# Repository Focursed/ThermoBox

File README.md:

# ThermoBox — карманный термометр с играми на одну кнопку

**Автор:** Igor Novohatskiy, 2026

Маленькая коробочка: экран 0,96" OLED, датчик SHT40, аккумулятор LiPo, зарядка от USB‑C,
боковая кнопка будит устройство из глубокого сна. Программируется через тот же USB‑C прямо из Arduino IDE.

## Схема электрическая принципиальная

Схема в PDF: [docs/ThermoBox_schematic.pdf](docs/ThermoBox_schematic.pdf) · исходник KiCad 10: [ThermoBox.kicad_sch](ThermoBox.kicad_sch)

## Печатная плата

## Структура проекта

| Путь | Что внутри |
|---|---|
| `ThermoBox.kicad_pro / .kicad_sch / .kicad_pcb` | проект KiCad 10 (схема + плата) |
| `docs/schematic.png`, `docs/ThermoBox_schematic.pdf` | схема (картинка и PDF) |
| `docs/ThermoBox_pcb_top.pdf`, `docs/board_*_3d.png` | плата |
| `fab/gerbers/` | Gerber + сверловка для заказа (JLCPCB/PCBWay: заархивируй папку в zip) |
| `fab/ThermoBox_BOM.csv`, `fab/ThermoBox_positions.csv` | список компонентов и координаты для сборки |
| `fusion/` | **STEP, DXF контура и все размеры для корпуса** — см. [fusion/DIMENSIONS.md](fusion/DIMENSIONS.md) |
| `fusion/case/` | корпус: основание и крышка (STL для печати, STEP, F3D) |
| `firmware/ThermoBox/ThermoBox.ino` | прошивка для Arduino IDE |

## Как устроена схема (и почему так)

| Узел | Решение | Зачем |
|---|---|---|
| МК | **ESP32‑C3‑WROOM‑02** | встроенный USB: прошивка из Arduino IDE без отдельного USB‑UART; глубокий сон ~5 мкА; пробуждение по кнопке (GPIO3) |
| USB‑C | резисторы 5,1 кОм на CC1/CC2, предохранитель PTC 500 мА, ESD‑защита USBLC6‑2SC6 | работает с любым кабелем C‑C и A‑C; защита от статики и КЗ |
| Зарядка | **MCP73831**, ток **≈210 мА** (R3 = 4,7 кОм) | линейная зарядка: тепло = (5 В − Vбат) × I. При 210 мА это ≈0,3 Вт — чип тёплый, но не горячий. Аккумулятор 1000 мА·ч заряжается ≈5–5,5 ч. Для быстрой зарядки (≈300 мА) поставь R3 = 3,3 кОм — будет заметно горячее |
| Питание от USB или батареи | P‑MOSFET AO3401A + диод Шоттки SS14 (power path) | при подключённом USB устройство питается от USB, а аккумулятор только заряжается; без USB — питание от аккумулятора без потерь на диоде |
| 3,3 В | LDO ME6211C33 | ток покоя ~40 мкА; можно заменить на RT9080‑33 / XC6220B331 (тот же корпус и распиновка) — ток покоя 1–2 мкА, сон станет ещё дольше |
| Экран и SHT40 | питаются через ключ Q2 (линия **VPER**); подтяжки I²C тоже на VPER | во сне экран и датчик полностью обесточены, ничего не «подпитывается» через линии I²C |
| SHT40 | на отдельном **язычке**, соединённом с платой узким перешейком (5 мм), без меди на нижнем слое; в 45–50 мм от зарядки | тепло от зарядки, LDO и ESP32 почти не доходит до датчика; меряется температура воздуха, а не платы. Датчик опрашивается сразу после пробуждения, пока МК холодный |
| Измерения | VBAT/2 → GPIO1 (1 МОм + 1 МОм + 100 нФ), VBUS/2 → GPIO0 | уровень заряда в % и значок зарядки |
| Кнопки | SW1 — **боковая** (EVQ‑P7A) на GPIO3 с подтяжкой 100 кОм и RC‑антидребезгом; SW2 RESET, SW3 BOOT | SW1: пробуждение и игры; RESET/BOOT нужны только для аварийной прошивки |
| Индикатор | красный LED D2 горит во время зарядки | |

### Надписи на плате
На нижней стороне платы (шелкография) крупно напечатаны название **ThermoBox v1.0**, назначение («Кишеньковий термометр‑гігрометр та маленька консоль»), состав и **Автор: Igor Novohatskiy, 2026**.

### Тепло на плате
* Зарядка (U2), LDO (U3), диод D1 и MOSFET Q1 стоят в нижнем левом углу, у USB, подальше от датчика.
* Земля залита на обоих слоях и сшита ~140 переходными отверстиями: медь работает как радиатор.
* Силовые дорожки шириной 0,4 мм, сигнальные — 0,2 мм.
* Под антенной ESP32 меди нет (зона запрета), иначе Wi‑Fi/BLE будет работать плохо.

### Сколько проработает
* Сон: ESP32‑C3 ≈ 5 мкА + LDO ≈ 40 мкА + делитель ≈ 2 мкА ≈ **50 мкА** → 1000 мА·ч хватит примерно на 2 года чистого сна.
* Пробуждение на 10 с ≈ 35–40 мА. 20 просмотров в день ≈ 3–4 мА·ч в сутки → **≈ 8–10 месяцев** на одном заряде.
* Игры: ≈ 40 мА → около **25 часов** непрерывной игры.

## Прошивка через Arduino IDE

1. **Arduino IDE 2.x** → *File → Preferences → Additional boards manager URLs*:
   `https://espressif.github.io/arduino-esp32/package_esp32_index.json`
2. *Boards Manager* → установи **esp32 by Espressif Systems** (версия 3.x).
3. *Library Manager* → установи **U8g2** (by olikraus). Для SHT40 библиотека не нужна: он читается напрямую.
4. *Tools*:
   * Board: **ESP32C3 Dev Module**
   * USB CDC On Boot: **Enabled**
   * Flash Size: 4MB
   * Port: появившийся COM‑порт
5. Открой `firmware/ThermoBox/ThermoBox.ino` → **Upload**.

> **Важно:** в глубоком сне USB отключается. Перед прошивкой нажми боковую кнопку: пока подключён USB, устройство не засыпает 60 с.
> Если прошивка всё равно не находит порт (например, программа сразу уходит в сон или зависла):
> **зажми BOOT → нажми и отпусти RESET → отпусти BOOT**, затем Upload. После прошивки нажми RESET.

### Управление
| Действие | Результат |
|---|---|
| нажатие во сне | проснуться, показать температуру, влажность и заряд |
| короткое нажатие | экран «Температура» ↔ «Статистика» (мин/макс, напряжение, USB) |
| долгое нажатие (0,7 с) | меню игр |
| в меню: коротко / долго | следующая игра / запустить |
| 10 с без нажатий | глубокий сон (60 с, если подключён USB) |

Каждые 10 минут устройство тихо просыпается примерно на 30 мс и обновляет мин/макс температуры
(`LOG_INTERVAL_S` в прошивке; `0` — выключить).

### Игры (всё управление — одной кнопкой)
* **Cave Flyer** — держи кнопку, чтобы набирать высоту, отпусти, чтобы снижаться; пролетай в просветы.
* **Jump Runner** — нажимай, чтобы перепрыгивать блоки; скорость растёт.
* **Reaction** — дождись «GO!» и нажми как можно быстрее; результат в миллисекундах.

Рекорды сохраняются во флеш‑памяти (`Preferences`) и не пропадают при выключении питания.

### Как добавить свою игру
```cpp
uint32_t gameMyGame() {        // вернуть счёт
  uint32_t t = 0, score = 0;
  while (true) {
    if (!frameDue(t)) continue;        // ~30 кадров/с
    if (btnDown()) { /* ... */ }       // кнопка зажата
    oled.clearBuffer(); /* рисуем */ oled.sendBuffer();
    if (/* проигрыш */ false) return score;
  }
}
// и одна строка в массив GAMES[]:
//   {"My Game", gameMyGame, false},   // false = больше очков — лучше
```

## Сборка и проверка

1. Закажи плату по `fab/gerbers` (2 слоя, 1,6 мм; дорожки/зазоры ≥ 0,15 мм, отверстия ≥ 0,2 мм — стандартные возможности JLCPCB/PCBWay).
   Монтаж односторонний, все детали сверху: можно заказать сборку по `ThermoBox_BOM.csv` и `ThermoBox_positions.csv`.
2. Сначала без аккумулятора и экрана подключи USB: на `+3V3` должно быть 3,3 В, а светодиод зарядки погаснет или будет мигать (аккумулятора нет — это нормально).
3. Подключи аккумулятор, **проверив полярность** (пин 1 = «+»).
4. Экран: впаяй модуль его же штырями в J3, с пластиковой проставкой 2,5 мм (порядок пинов на модуле: **GND, VCC, SCL, SDA**; бывают модули с VCC‑GND — проверь надписи!).
5. Если изображение сдвинуто на 2 пикселя — у тебя контроллер SH1106: переключи строку `oled(...)` в начале прошивки.

## Проверки
* ERC схемы — 0 ошибок, 0 предупреждений.
* DRC платы — 0 ошибок, 0 неразведённых связей; осталось 2 предупреждения: шелкография самого USB‑разъёма заходит на край платы (так устроен посадочный шаблон, на производство не влияет).

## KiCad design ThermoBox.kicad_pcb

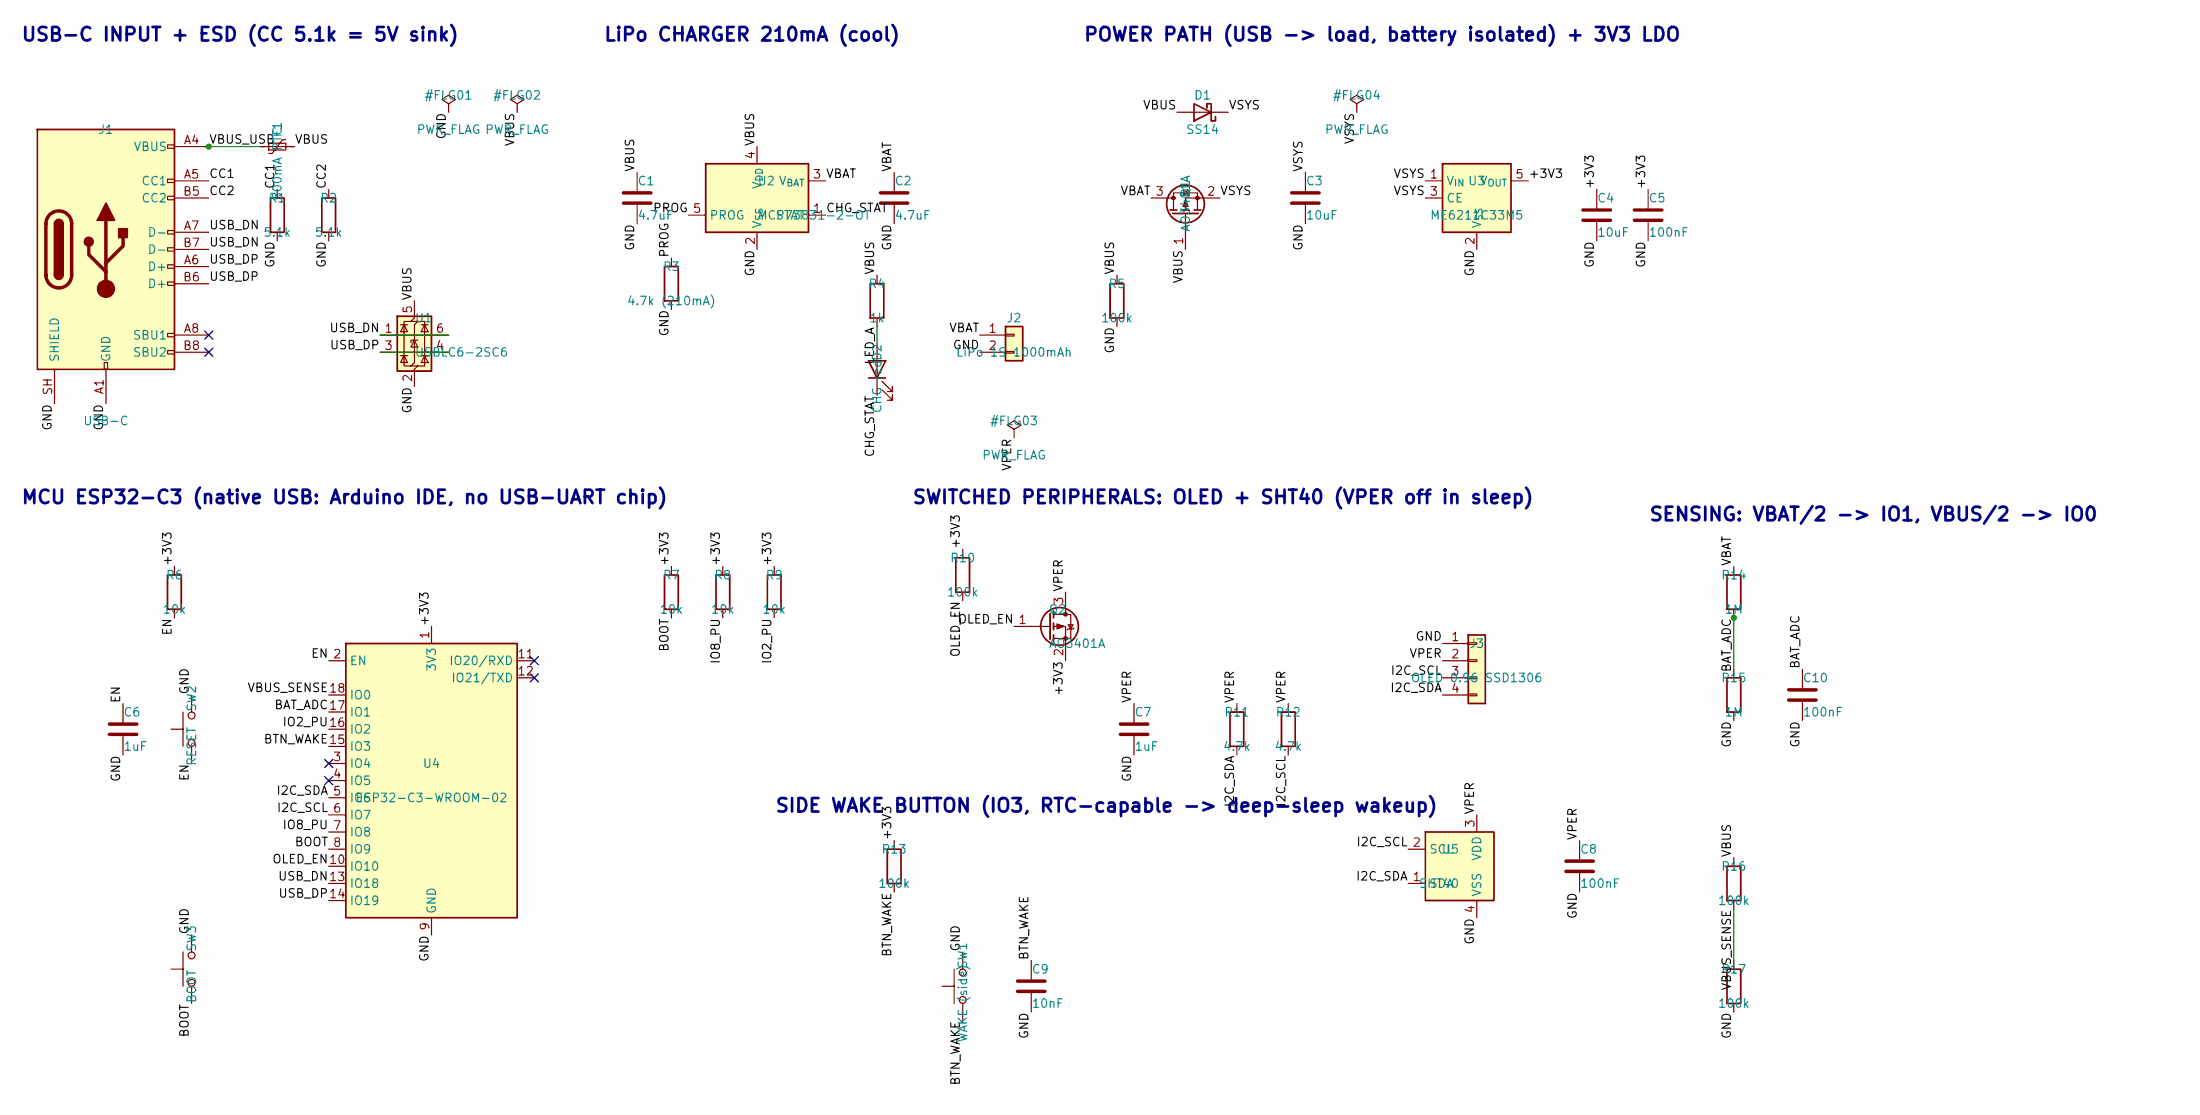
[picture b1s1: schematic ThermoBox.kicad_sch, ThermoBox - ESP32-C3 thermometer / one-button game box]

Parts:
C1, C2: 4.7uF; C_0805_2012Metric
C3, C4: 10uF; C_0805_2012Metric
C5, C8, C10: 100nF; C_0603_1608Metric
C6, C7: 1uF; C_0603_1608Metric
C9: 10nF; C_0603_1608Metric
D1: SS14; D_SMA
D2: CHG red; LED_0603_1608Metric
F1: 500mA PTC; Fuse_1206_3216Metric
J1: USB-C; USB_C_Receptacle_HRO_TYPE-C-31-M-12
J2: LiPo 1S 1000mAh; JST_PH_S2B-PH-SM4-TB_1x02-1MP_P2.00mm_Horizontal
J3: OLED 0.96 SSD1306; PinHeader_1x04_P2.54mm_Vertical
Q1, Q2: AO3401A; SOT-23
R1, R2: 5.1k; R_0603_1608Metric
R3: 4.7k (210mA); R_0603_1608Metric
R4: 1k; R_0603_1608Metric
R5, R10, R13, R16, R17: 100k; R_0603_1608Metric
R6, R7, R8, R9: 10k; R_0603_1608Metric
R11, R12: 4.7k; R_0603_1608Metric
R14, R15: 1M; R_0603_1608Metric
SW1: WAKE (side); SW_SPST_EVQP7A
SW2: RESET; SW_Push_SPST_NO_Alps_SKRK
SW3: BOOT; SW_Push_SPST_NO_Alps_SKRK
U1: USBLC6-2SC6; SOT-23-6
U2: MCP73831-2-OT; SOT-23-5
U3: ME6211C33M5; SOT-23-5
U4: ESP32-C3-WROOM-02
U5: SHT40; Sensirion_DFN-4_1.5x1.5mm_P0.8mm_SHT4x_NoCentralPad

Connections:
/+3V3: C4.1, C5.1, Q2.2 (S), R6.1, R7.1, R8.1, R9.1, R10.1, R13.1, U3.5 (V_{OUT}), U4.1 (3V3)
/BAT_ADC: C10.1, R14.2, R15.1, U4.17 (IO1)
/BOOT: R7.2, SW3.1, U4.8 (IO9)
/BTN_WAKE: C9.1, R13.2, SW1.1, U4.15 (IO3)
/CC1: J1.A5 (CC1), R1.1
/CC2: J1.B5 (CC2), R2.1
/CHG_STAT: D2.1 (K), U2.1 (STAT)
/EN: C6.1, R6.2, SW2.1, U4.2 (EN)
/GND: C1.2, C2.2, C3.2, C4.2, C5.2, C6.2, C7.2, C8.2, C9.2, C10.2, J1.A1 (GND), J1.A12 (GND), J1.B1 (GND), J1.B12 (GND), J1.SH (SHIELD), J2.2, J3.1, R1.2, R2.2, R3.2, R5.2, R15.2, R17.2, SW1.2, SW2.2, SW3.2, U1.2 (GND), U2.2 (V_{SS}), U3.2 (V_{SS}), U4.9 (GND), U4.19 (GND), U5.4 (VSS)
/I2C_SCL: J3.3, R12.2, U4.6 (IO7), U5.2 (SCL)
/I2C_SDA: J3.4, R11.2, U4.5 (IO6), U5.1 (SDA)
/IO2_PU: R9.2, U4.16 (IO2)
/IO8_PU: R8.2, U4.7 (IO8)
/LED_A: D2.2 (A), R4.2
/OLED_EN: Q2.1 (G), R10.2, U4.10 (IO10)
/PROG: R3.1, U2.5 (PROG)
/USB_DN: J1.A7 (D-), J1.B7 (D-), U1.1 (I/O1), U1.6 (I/O1), U4.13 (IO18)
/USB_DP: J1.A6 (D+), J1.B6 (D+), U1.3 (I/O2), U1.4 (I/O2), U4.14 (IO19)
/VBAT: C2.1, J2.1, Q1.3 (D), R14.1, U2.3 (V_{BAT})
/VBUS: C1.1, D1.2 (A), F1.2, Q1.1 (G), R4.1, R5.1, R16.1, U1.5 (VBUS), U2.4 (V_{DD})
/VBUS_SENSE: R16.2, R17.1, U4.18 (IO0)
/VBUS_USB: F1.1, J1.A4 (VBUS), J1.A9 (VBUS), J1.B4 (VBUS), J1.B9 (VBUS)
/VPER: C7.1, C8.1, J3.2, Q2.3 (D), R11.1, R12.1, U5.3 (VDD)
/VSYS: C3.1, D1.1 (K), Q1.2 (S), U3.1 (V_{IN}), U3.3 (CE)

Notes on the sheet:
USB-C INPUT + ESD (CC 5.1k = 5V sink)
LiPo CHARGER 210mA (cool)
POWER PATH (USB -> load, battery isolated) + 3V3 LDO
MCU ESP32-C3 (native USB: Arduino IDE, no USB-UART chip)
SWITCHED PERIPHERALS: OLED + SHT40 (VPER off in sleep)
SENSING: VBAT/2 -> IO1, VBUS/2 -> IO0
SIDE WAKE BUTTON (IO3, RTC-capable -> deep-sleep wakeup)

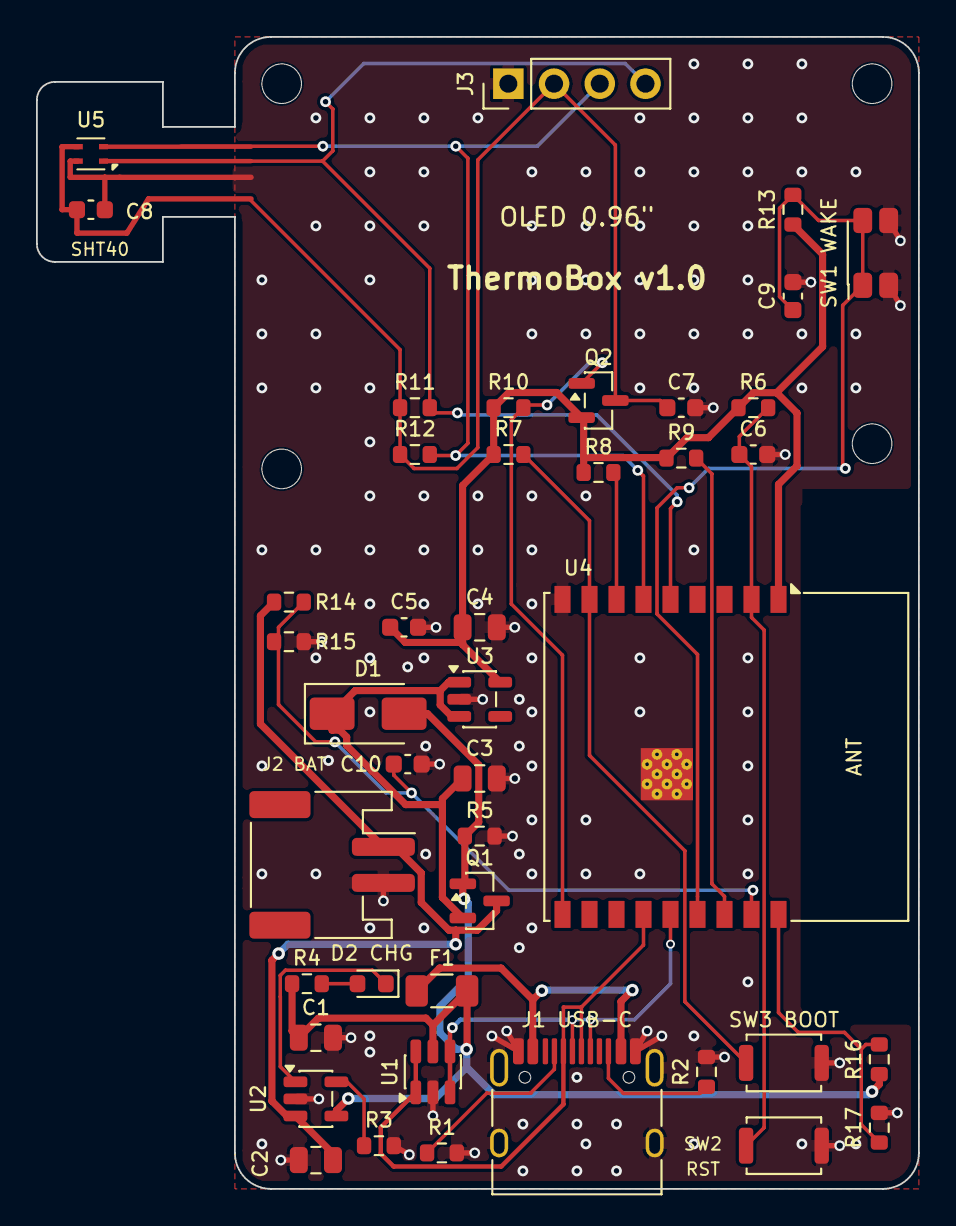
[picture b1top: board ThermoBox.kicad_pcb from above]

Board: 2 copper layers, 49.0 x 64.0 mm, 47 parts (0 on the bottom side), 24 nets.

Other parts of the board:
H1, H2, H3, H4: MountingHole_2.2mm_M2

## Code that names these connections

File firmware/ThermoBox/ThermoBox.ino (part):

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    no presses for 10 s -> deep sleep (60 s while USB is plugged in)

  Hardware map (see schematic):
    GPIO3  BTN_WAKE   active LOW, 100k pull-up, RTC-capable -> deep sleep wake
    GPIO6  I2C_SDA    GPIO7 I2C_SCL  (pull-ups on the switched VPER rail)
    GPIO10 OLED_EN    LOW = OLED + SHT40 powered (P-MOSFET Q2), 100k pull-up = off
    GPIO1  BAT_ADC    VBAT / 2
    GPIO0  VBUS_SENSE VBUS / 2 (HIGH when USB is plugged in)
*/
#include <Arduino.h>
#include <Wire.h>
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constexpr int PIN_BTN = 3;
constexpr int PIN_SDA = 6;
constexpr int PIN_SCL = 7;
constexpr int PIN_OLED_EN = 10;
constexpr int PIN_BAT = 1;
constexpr int PIN_VBUS = 0;

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
// ------------------------------------------------------------------ power
void peripheralsOn() {
  pinMode(PIN_OLED_EN, OUTPUT);
  digitalWrite(PIN_OLED_EN, LOW);   // P-MOSFET on
  delay(5);                          // SHT40 needs 1 ms, OLED a little more
  Wire.begin(PIN_SDA, PIN_SCL, 400000);
}
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  Wire.end();
  pinMode(PIN_SDA, INPUT);           // never drive pins into an unpowered chip
  pinMode(PIN_SCL, INPUT);
  pinMode(PIN_OLED_EN, INPUT);       // external 100k pull-up keeps Q2 off in sleep
}

bool usbPresent() { return digitalRead(PIN_VBUS) == HIGH; }
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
